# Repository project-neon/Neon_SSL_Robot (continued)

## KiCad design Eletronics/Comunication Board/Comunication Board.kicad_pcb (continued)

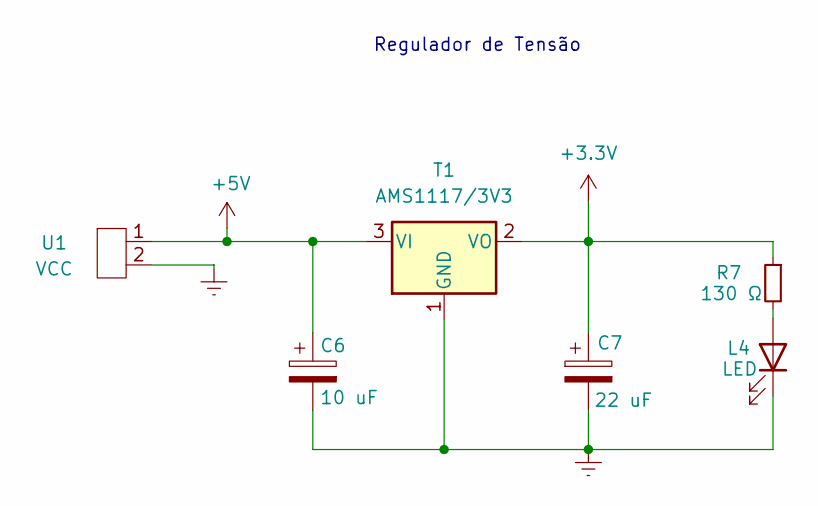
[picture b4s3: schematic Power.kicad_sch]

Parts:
C6: 10 uF; C_0603_1608Metric
C7: 22 uF; C_0603_1608Metric
L4: LED; LED_0603_1608Metric
R7: 130 Ω; R_0603_1608Metric
T1: AMS1117/3V3; SOT-223-3_TabPin2
U1: VCC; JST_XH_B2B-XH-AM_1x02_P2.50mm_Vertical

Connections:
+3.3V: C7.1, R7.1, T1.2 (VO); also elsewhere on the board
+5V: C6.1, T1.3 (VI), U1.1; also elsewhere on the board
GNDREF: C6.2, C7.2, L4.1 (K), T1.1 (GND), U1.2; also elsewhere on the board
unnamed: L4.2 (A), R7.2

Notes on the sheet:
Regulador de Tensão

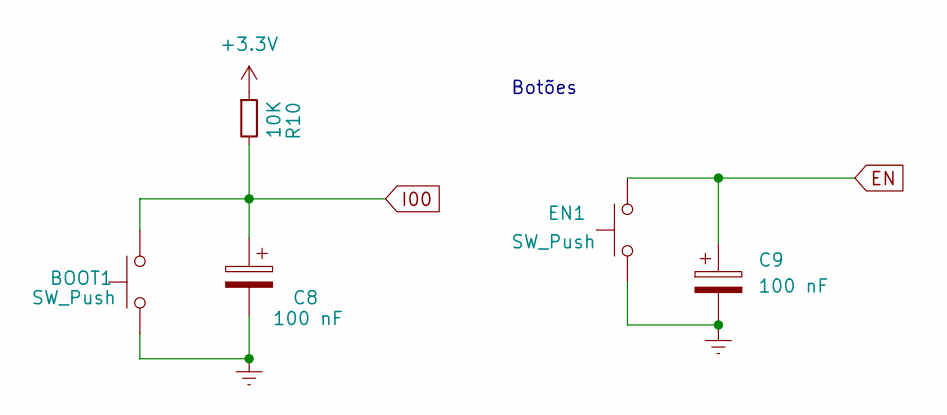
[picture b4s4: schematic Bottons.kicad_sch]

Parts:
BOOT1: SW_Push; SW_SPST_TL3305A
C8, C9: 100 nF; C_0603_1608Metric
EN1: SW_Push; SW_SPST_TL3305A
R10: 10K; R_0603_1608Metric

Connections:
+3.3V: R10.1; also elsewhere on the board
GNDREF: BOOT1.2, C8.2, C9.2, EN1.2; also elsewhere on the board

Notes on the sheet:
Botões

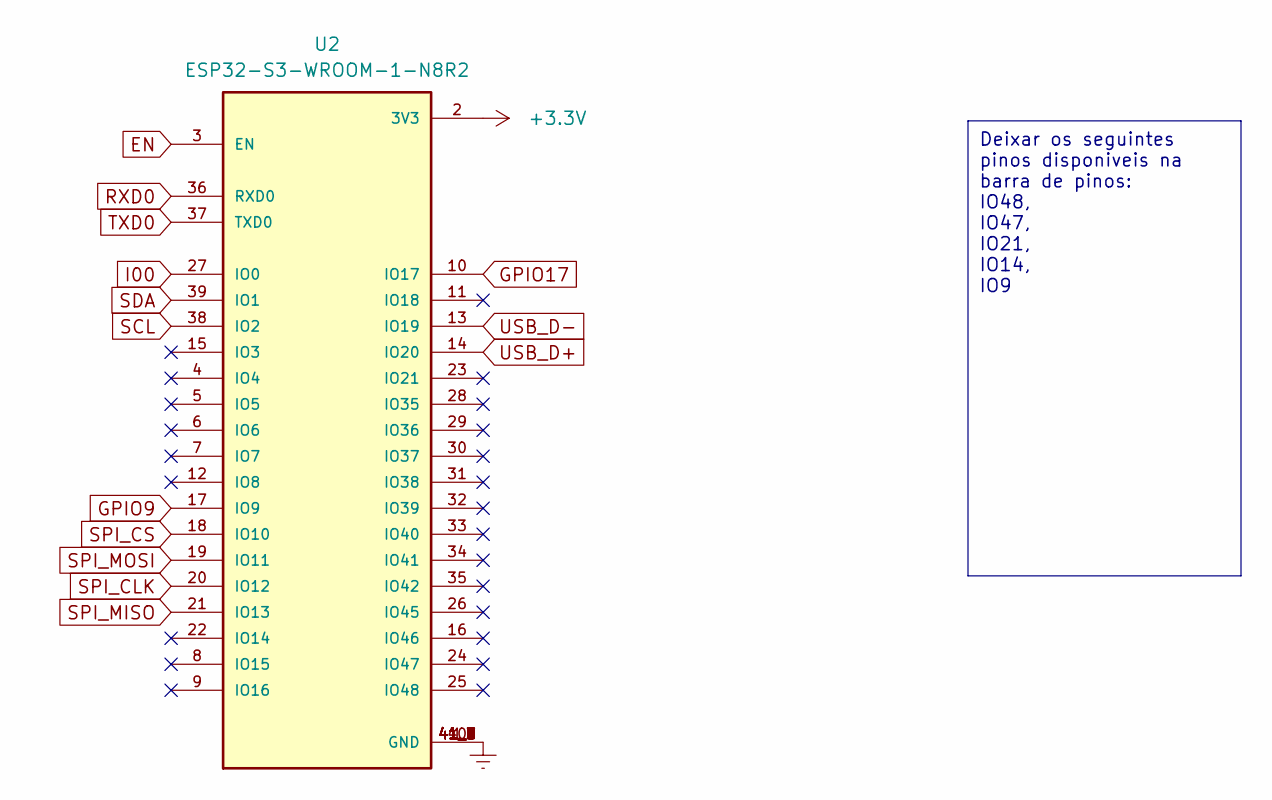
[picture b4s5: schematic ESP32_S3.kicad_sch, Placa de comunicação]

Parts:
U2: ESP32-S3-WROOM-1-N8R2; XCVR_ESP32-S3-WROOM-1-N8R2; PARTREV v1.0

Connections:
+3.3V: U2.2 (3V3); also elsewhere on the board
GNDREF: U2.1 (GND), U2.40 (GND), U2.41_1 (GND), U2.41_2 (GND), U2.41_3 (GND), U2.41_4 (GND), U2.41_5 (GND), U2.41_6 (GND), U2.41_7 (GND), U2.41_8 (GND), U2.41_9 (GND), U2.41_10, U2.41_11, U2.41_12, U2.41_13, U2.41_14, U2.41_15, U2.41_16, U2.41_17, U2.41_18, U2.41_19, U2.41_20, U2.41_21; also elsewhere on the board
GPIO9: U2.17 (IO9); also elsewhere on the board
GPIO14: U2.22 (IO14); also elsewhere on the board
GPIO17: U2.10 (IO17); also elsewhere on the board
GPIO21: U2.23 (IO21); also elsewhere on the board
GPIO47: U2.24 (IO47); also elsewhere on the board
GPIO48: U2.25 (IO48); also elsewhere on the board
RXD0: U2.36 (RXD0); also elsewhere on the board
SCL: U2.38 (IO2); also elsewhere on the board
SDA: U2.39 (IO1); also elsewhere on the board
SPI_CLK: U2.20 (IO12); also elsewhere on the board
SPI_CS: U2.18 (IO10); also elsewhere on the board
SPI_MISO: U2.21 (IO13); also elsewhere on the board
SPI_MOSI: U2.19 (IO11); also elsewhere on the board
TXD0: U2.37 (TXD0); also elsewhere on the board
USB_D+: U2.14 (IO20); also elsewhere on the board
USB_D-: U2.13 (IO19); also elsewhere on the board

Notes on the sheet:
Deixar os seguintes pinos disponiveis na barra de pinos: IO48, IO47, IO21, IO14, IO9

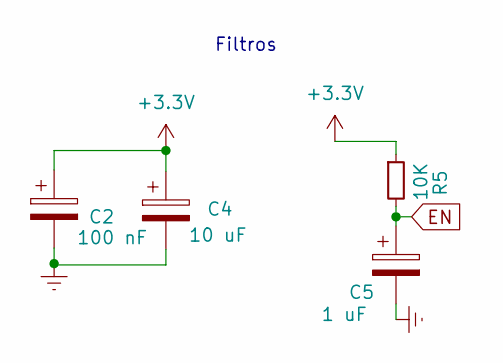
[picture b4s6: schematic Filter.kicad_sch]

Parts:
C2: 100 nF; C_0603_1608Metric
C4: 10 uF; C_0603_1608Metric
C5: 1 uF; C_0603_1608Metric
R5: 10K; R_0603_1608Metric

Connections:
+3.3V: C2.1, C4.1, R5.1; also elsewhere on the board
GNDREF: C2.2, C4.2, C5.2; also elsewhere on the board

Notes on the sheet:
Filtros

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
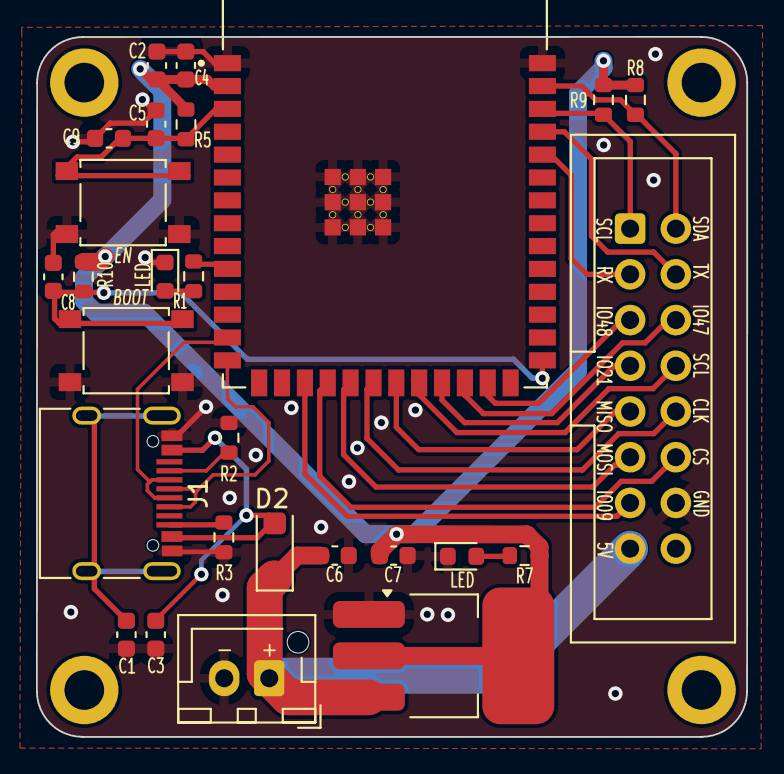
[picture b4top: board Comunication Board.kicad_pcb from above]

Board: 2 copper layers, 39.5 x 38.9 mm, 32 parts (1 on the bottom side), 27 nets.

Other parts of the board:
1, 2, 3, 4: MountingHole_2.2mm_M2_DIN965_Pad
EN1#2: SW_Push; SW_SPST_TL3305A
G: LOGO; Logo.Neon

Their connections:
GNDREF: EN1#2.2; also elsewhere on the board

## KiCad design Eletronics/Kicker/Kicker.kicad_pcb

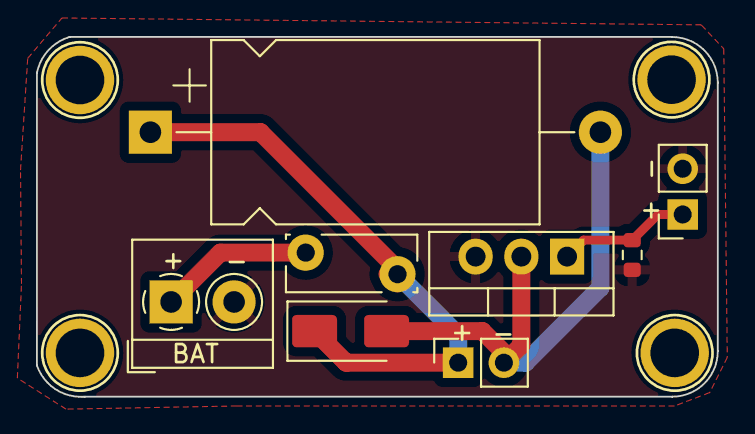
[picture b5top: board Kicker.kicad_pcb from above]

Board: 2 copper layers, 37.8 x 20.0 mm, 13 parts (1 on the bottom side), 5 nets.

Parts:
C1: 10 mF; CP_Axial_L18.0mm_D10.0mm_P25.00mm_Horizontal
D1: 1N4007; D_SMA
F2: Fuse_Polarized; Fuse_Bourns_MF-RG300
G: LOGO; Logo.Neon
H4, H4#2, H4#3, H4#4: MountingHole; MountingHole_M2.5_SirBoard
J1: Solenoid; PinSocket_1x02_P2.54mm_Vertical
J2: Signal; PinSocket_1x02_P2.54mm_Vertical
J3: Battery; TerminalBlock_4Ucon_1x02_P3.50mm_Horizontal
Q1: IRF540N; TO-220-3_Vertical
R1: 1K; R_0603_1608Metric

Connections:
+BATT: F2.1, J3.1
GNDREF: J2.2, J3.2, Q1.3 (S), R1.2
unnamed: C1.2, D1.2 (A), J1.2, Q1.2 (D)
unnamed: C1.1, D1.1 (K), F2.2, J1.1
unnamed: J2.1, Q1.1 (G), R1.1

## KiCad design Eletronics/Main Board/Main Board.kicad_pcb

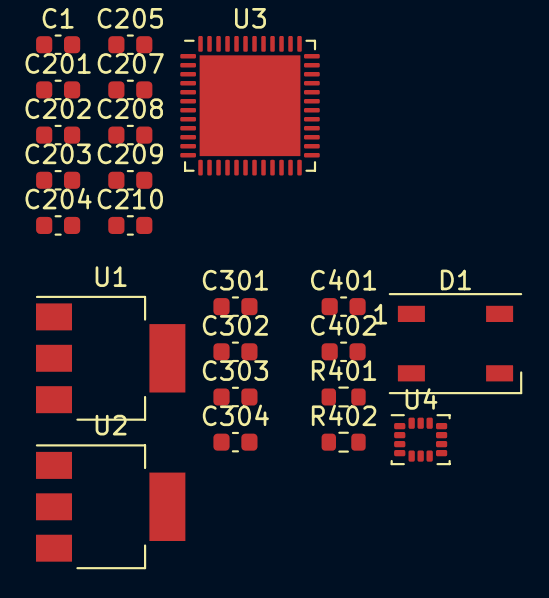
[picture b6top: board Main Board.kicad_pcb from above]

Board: 2 copper layers, 23 parts (0 on the bottom side), 13 nets, no tracks yet.

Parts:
C1: 2.2uF; C_0603_1608Metric
C201, C301, C304: 10uF; C_0603_1608Metric
C202, C203, C204, C205, C401, C402: 100nF; C_0603_1608Metric
C207, C208: 4.3pF; C_0603_1608Metric
C209, C210: 12 pF; C_0603_1608Metric
C302, C303: 22nF; C_0603_1608Metric
D1: WS2812B; LED_WS2812B_PLCC4_5.0x5.0mm_P3.2mm
R401, R402: 10k; R_0603_1608Metric
U1: AMS1117-5.0; SOT-223-3_TabPin2
U2: AMS1117-3.3; SOT-223-3_TabPin2
U3: STM32F411CEUx; QFN-48-1EP_7x7mm_P0.5mm_EP5.6x5.6mm
U4: LSM6DSL; LGA-14_3x2.5mm_P0.5mm_LayoutBorder3x4y

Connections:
+3.3V: C401.1, C402.1, R401.1, R402.1, U4.5 (VDDIO), U4.8 (VDD)
+3V3: C201.1, C202.1, C203.1, C204.1, C205.1, C303.1, U2.2 (VO)
+5V: C302.1, C304.1, D1.1 (VDD), U1.2 (VO), U2.3 (VI)
+BATT: C301.1, U1.3 (VI)
/Peripherals Circuit/SCL: R402.2, U4.13 (SCL)
/Peripherals Circuit/SDA: R401.2, U4.14 (SDA)
GND: C1.2, C201.2, C202.2, C203.2, C204.2, C205.2, C207.1, C208.1, C209.1, C210.1, C301.2, C302.2, C303.2, C304.2, C401.2, C402.2, D1.3 (VSS), U1.1 (GND), U2.1 (GND), U4.2 (SDX), U4.3 (SCX), U4.6 (GND), U4.7 (GND)
unnamed: C207.2, U3.3 (PC14)
unnamed: C208.2, U3.4 (PC15)
unnamed: C209.2, U3.5 (PH0)
unnamed: C210.2, U3.6 (PH1)
unnamed: C1.1, U3.22 (VCAP1)
unnamed: U3.23 (VSS), U3.35 (VSS), U3.47 (VSS), U3.49 (VSS)

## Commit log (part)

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2023-05-01 [ADDED] Main Components
2023-05-18 Perifericos ok
2023-05-21 First commit - comunication board
2023-05-24 Comunication Board edit
2023-06-08 Power ok
2023-06-12 Comunication board
2023-06-14 update sch
2023-07-02 Design Commutication Board pcb
2023-07-03 Communication board schematic
2023-07-26 Communication board ok
2023-08-15 alteracoes finais
2023-08-31 Kicker pcb
2023-09-11 BOM List
2024-03-21 Kicker modified
2024-03-21 Comunication Board Errors solved
2024-06-05 kicker modification
2024-06-07 Revisão com alterações apontadas no esquemático
2024-07-06 edit communication board
2024-07-12 modificacoes communication board
2024-07-19 Mudanças esquematico
2024-07-22 Communication Board edit
2024-08-27 revisão e pequenos ajustes de roteamento
2024-08-30 fix for manufacture
2024-08-30 small fixes
